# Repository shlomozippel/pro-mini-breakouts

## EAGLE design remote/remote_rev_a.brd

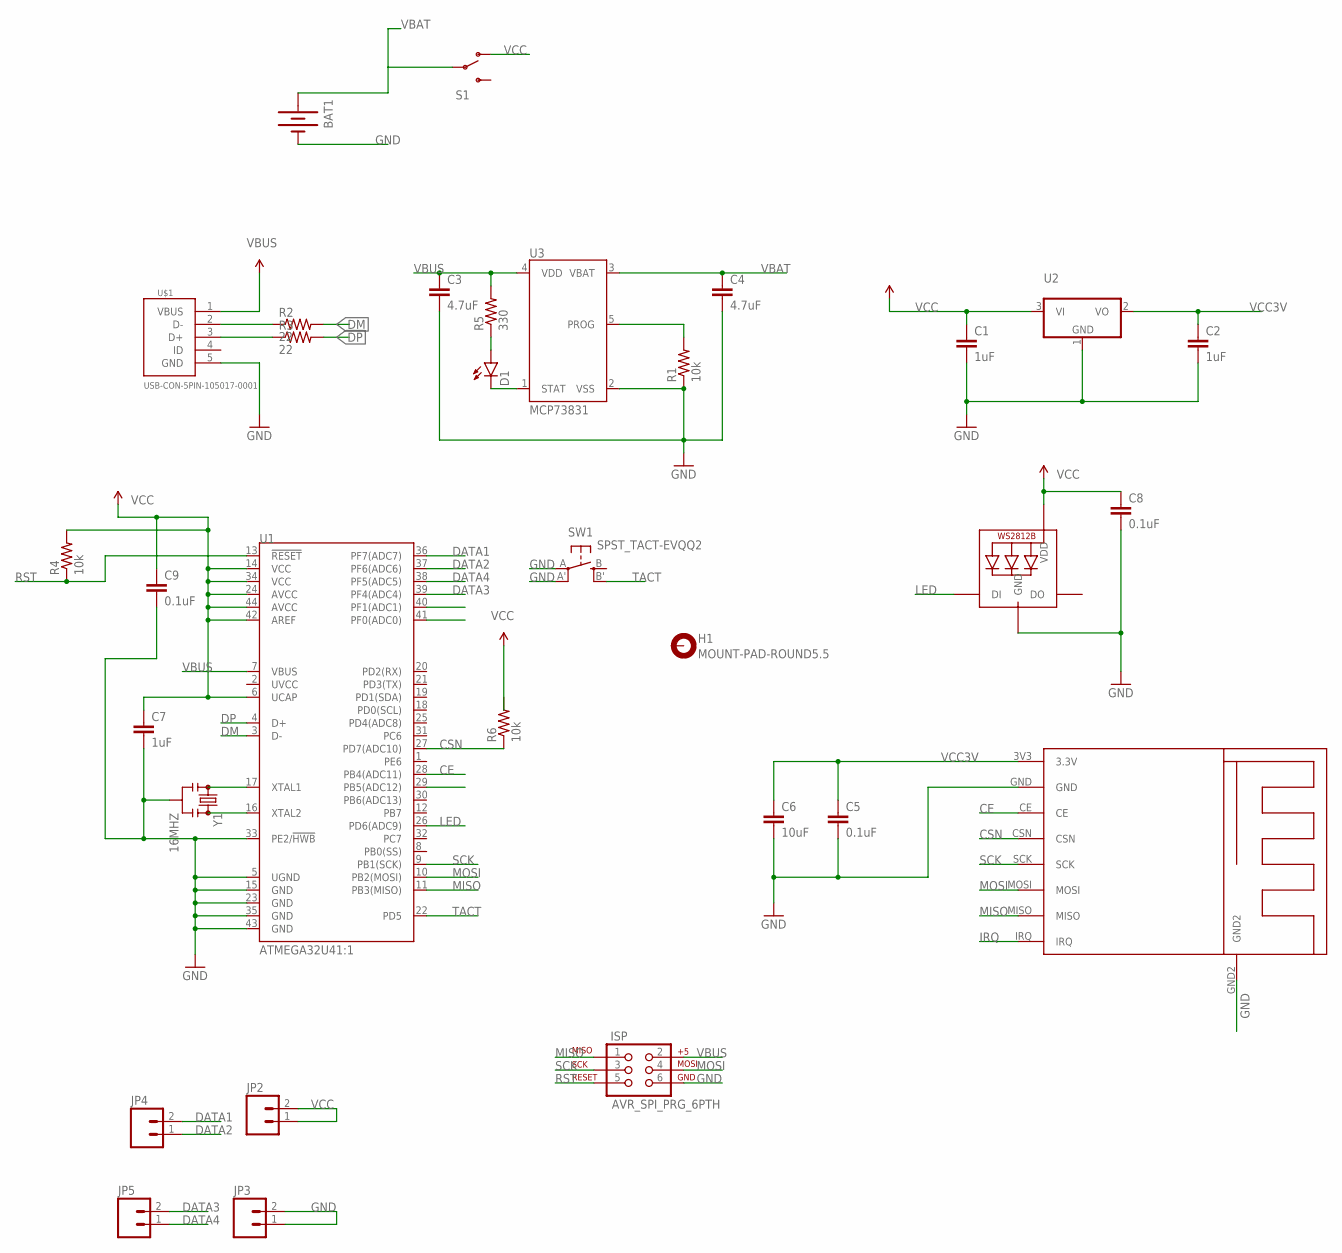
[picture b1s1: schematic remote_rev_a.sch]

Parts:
BAT1: BATTERY245PTH; BATTCON_245MM_PTH
C1, C2, C7: 1uF; 0603-CAP
C3, C4: 4.7uF; 0603-CAP
C5, C8, C9: 0.1uF; 0603-CAP
C6: 10uF; 0603-CAP
D1: LED0603; LED-0603
H1: MOUNT-PAD-ROUND5.5; 5,5-PAD
ISP: AVR_SPI_PRG_6PTH; 2X3
JP2, JP3, JP4, JP5: M02PTH; 1X02
LED1: WS2812B_5050N; WS2812B-NARROW
R1, R4, R6: 10k; 0603-RES
R2, R3: 22; 0603-RES
R5: 330; 0603-RES
S1: SWITCH-SPDTPTH; SWITCH-SPDT
SW1: SPST_TACT-EVQQ2; EVQ-Q2
U1: ATMEGA32U41:1; QFN-44-NOPAD_1:1
U2: AP2120N-3.0; SOT-23-3
U3: MCP73831; SOT23-5
U$1: USB-CON-5PIN-105017-0001; USB-MICRO-MOLEX-105017-0001
U$3: NRF24MINI
Y1: 16MHZ; RESONATOR-SMD

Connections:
CE: U1.28 (PB4(ADC11)), U$3.CE
CSN: R6.1, U1.27 (PD7(ADC10)), U$3.CSN
DATA1: JP4.2, U1.36 (PF7(ADC7))
DATA2: JP4.1, U1.37 (PF6(ADC6))
DATA3: JP5.2, U1.39 (PF4(ADC4))
DATA4: JP5.1, U1.38 (PF5(ADC5))
DM: R2.2, U1.3 (D-)
DP: R3.2, U1.4 (D+)
GND: BAT1.2 (-), C1.2, C2.2, C3.2, C4.2, C5.2, C6.2, C7.2, C8.2, C9.2, ISP.6, JP3.1, JP3.2, LED1.3-GND (GND), R1.1, SW1.A, SW1.A' (P1), U1.5 (UGND), U1.15 (GND), U1.23 (GND), U1.33 (PE2/!HWB), U1.35 (GND), U1.43 (GND), U2.1 (GND), U3.2 (VSS), U$1.5 (GND), U$3.GND, U$3.GND2, Y1.2
IRQ: U$3.IRQ
LED: LED1.4-DIN (DI), U1.26 (PD6(ADC9))
MISO: ISP.1, U1.11 (PB3(MISO)), U$3.MISO
MOSI: ISP.4, U1.10 (PB2(MOSI)), U$3.MOSI
unnamed: R1.2, U3.5 (PROG)
unnamed: R2.1, U$1.2 (D-)
unnamed: R3.1, U$1.3 (D+)
unnamed: U1.17 (XTAL1), Y1.1
unnamed: U1.16 (XTAL2), Y1.3
unnamed: D1.A, R5.1
unnamed: D1.C, U3.1 (STAT)
RST: ISP.5, R4.1, U1.13 (!RESET)
SCK: ISP.3, U1.9 (PB1(SCK)), U$3.SCK
TACT: SW1.B' (S1), U1.22 (PD5)
VBAT: BAT1.1 (+), BAT1.3 (+), C4.1, S1.2, U3.3 (VBAT)
VBUS: C3.1, ISP.2, R5.2, U1.7 (VBUS), U3.4 (VDD), U$1.1 (VBUS)
VCC: C1.1, C7.1, C8.1, C9.1, JP2.1, JP2.2, LED1.1-VDD (VDD), R4.2, S1.1 (O), U1.6 (UCAP), U1.14 (VCC), U1.24 (AVCC), U1.34 (VCC), U1.42 (AREF), U1.44 (AVCC), U2.3 (VI)
VCC3V: C2.1, C5.1, C6.1, U2.2 (VO), U$3.3V3 (3.3V)

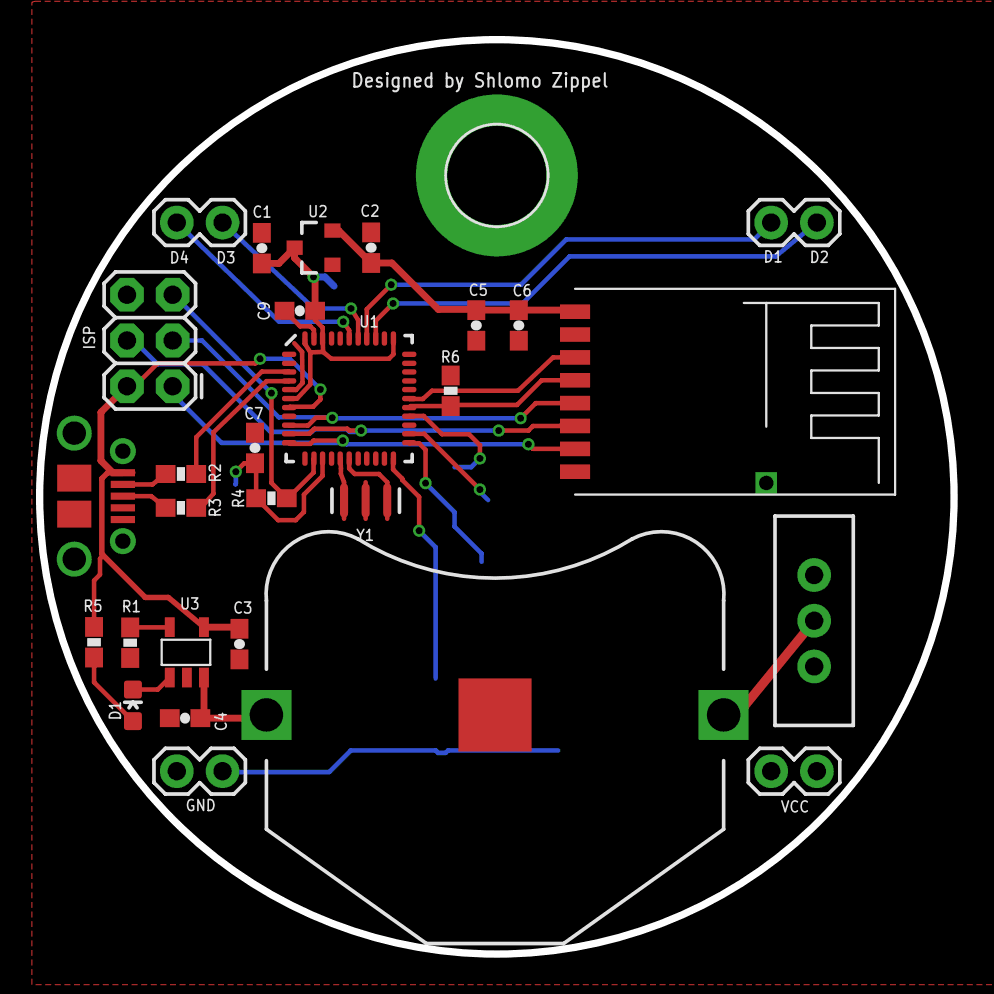
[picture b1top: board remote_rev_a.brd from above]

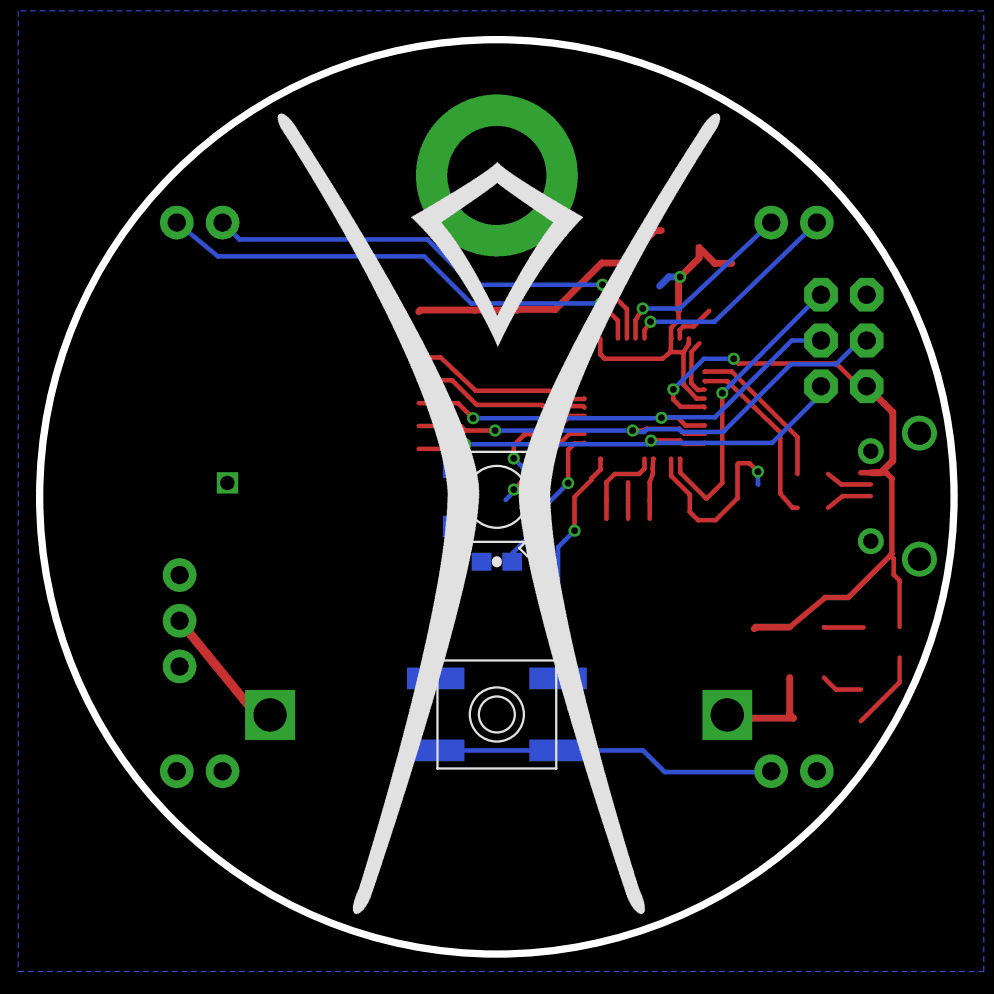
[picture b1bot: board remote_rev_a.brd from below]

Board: 2 copper layers, 50.8 x 50.8 mm, 32 parts (3 on the bottom side), 26 nets.

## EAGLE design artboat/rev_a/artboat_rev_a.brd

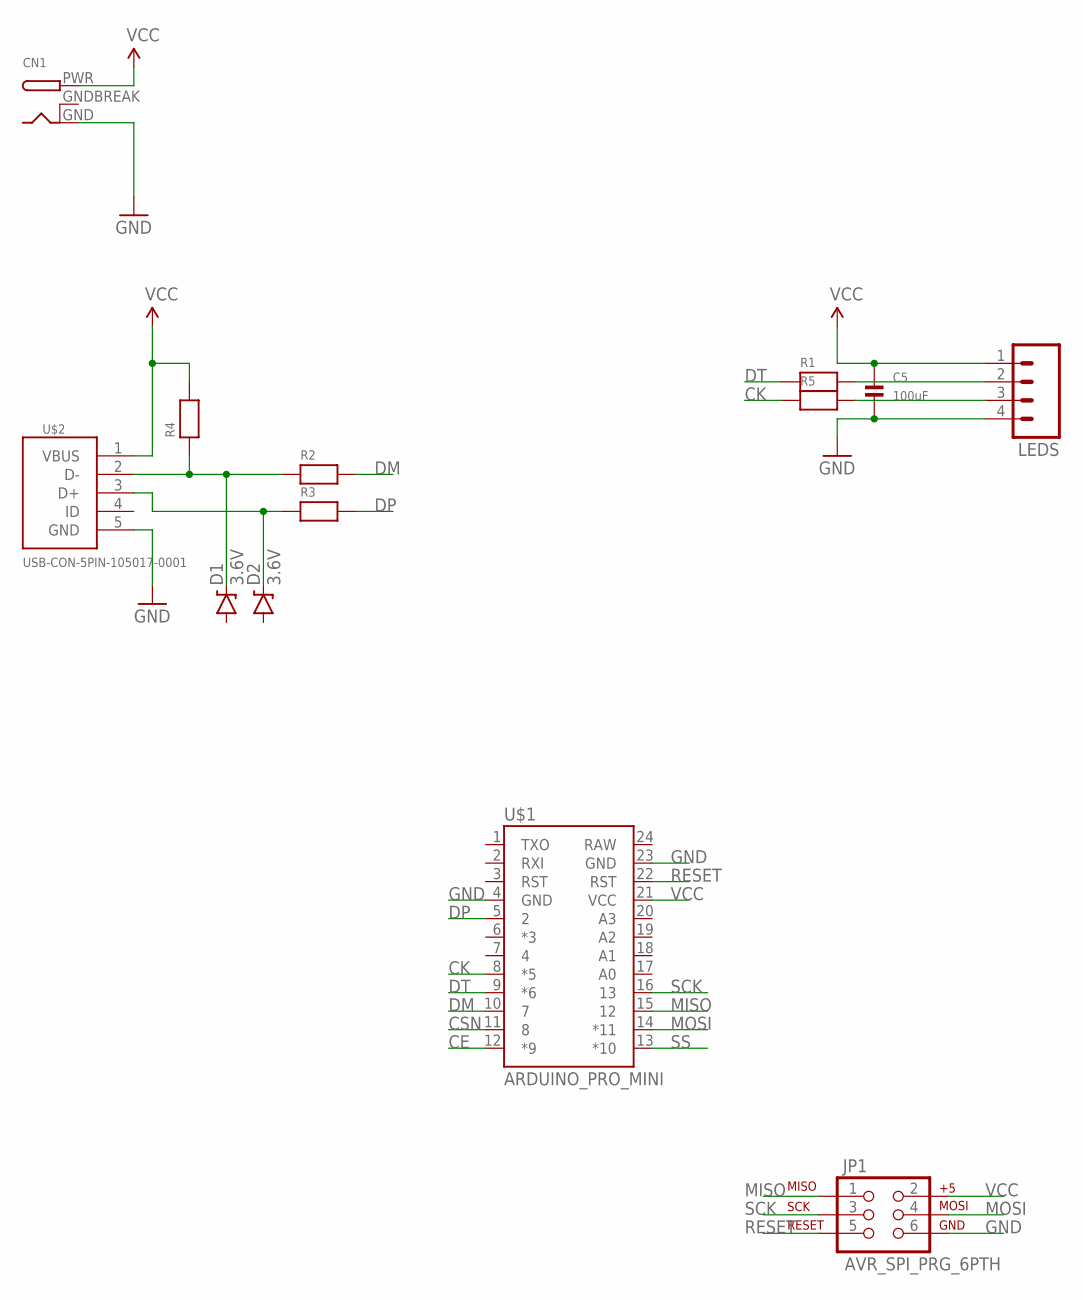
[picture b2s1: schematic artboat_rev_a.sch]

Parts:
C5: 100uF; 1206
CN1: DCBARRELPTH; DCJACK_2MM_PTH
D1, D2: 3.6V; SOD-323
JP1: AVR_SPI_PRG_6PTH; 2X3
LEDS: M04PTH; 1X04
R1, R2, R3, R4, R5: RESISTOR_0603; _0603
U$1: ARDUINO_PRO_MINI
U$2: USB-CON-5PIN-105017-0001; USB-MICRO-MOLEX-105017-0001

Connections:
CE: U$1.12 (*9)
CK: R5.1, U$1.8 (*5)
CSN: U$1.11 (8)
DM: R2.2, U$1.10 (7)
DP: R3.2, U$1.5 (2)
DT: R1.1, U$1.9 (*6)
GND: C5.2, CN1.GND, JP1.6, LEDS.4, U$1.4 (GND), U$1.23 (GND), U$2.5 (GND)
GNDBREAK: CN1.GNDBREAK
MISO: JP1.1, U$1.15 (12)
MOSI: JP1.4, U$1.14 (*11)
unnamed: LEDS.2, LEDS.3, R1.2, R5.2
unnamed: D1.C, R2.1, R4.1, U$2.2 (D-)
unnamed: D2.C, R3.1, U$2.3 (D+)
RESET: JP1.5, U$1.22 (RST)
SCK: JP1.3, U$1.16 (13)
SS: U$1.13 (*10)
VCC: C5.1, CN1.PWR, JP1.2, LEDS.1, R4.2, U$1.21 (VCC), U$2.1 (VBUS)

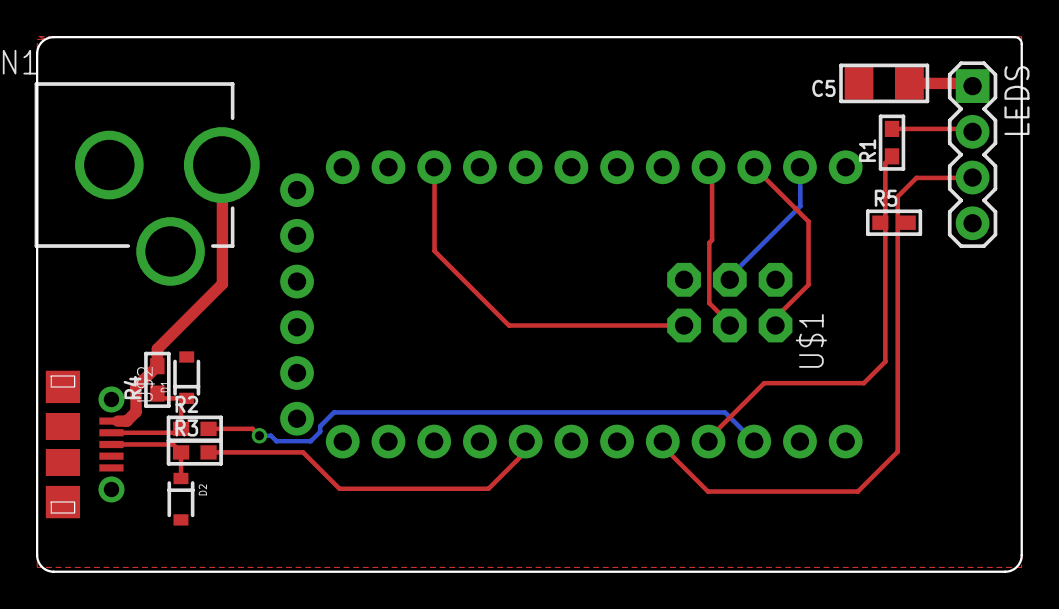
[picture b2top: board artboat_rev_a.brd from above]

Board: 2 copper layers, 54.7 x 29.7 mm, 14 parts (1 on the bottom side), 13 nets.

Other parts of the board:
U$5: 61*36-2

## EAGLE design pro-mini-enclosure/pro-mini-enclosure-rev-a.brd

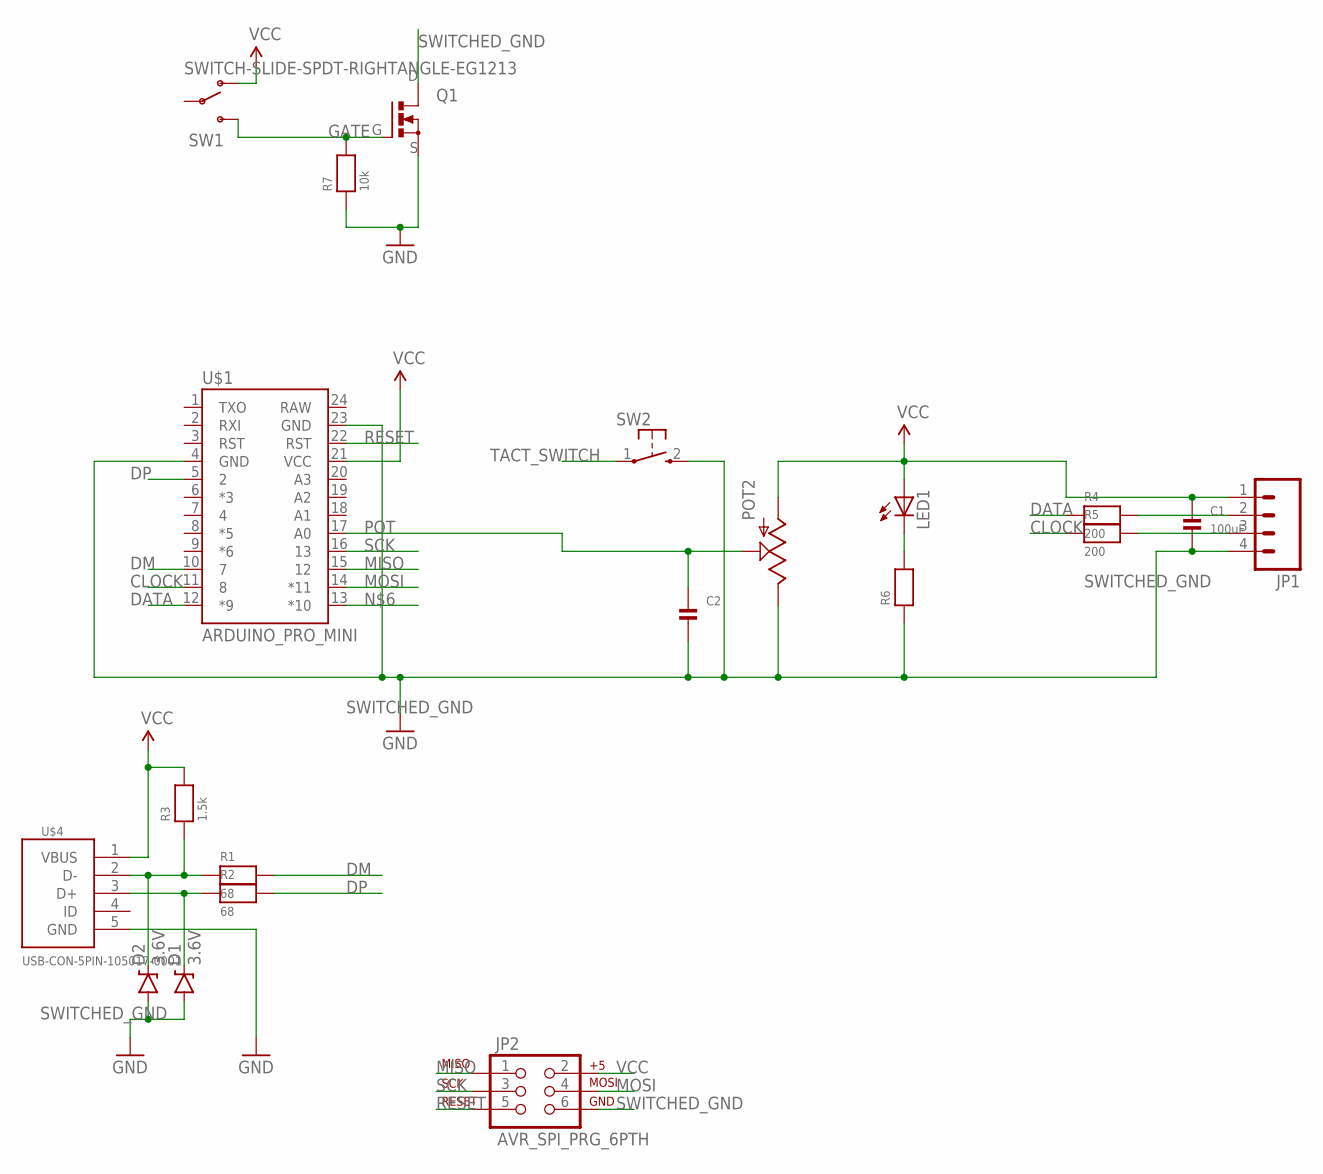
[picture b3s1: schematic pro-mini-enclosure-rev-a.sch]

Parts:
C1: 100uF; 1206
C2: CAP_CERAMIC0603MINI; 0603-MINI
D1, D2: 3.6V; SOD-323
JP1: M04PTH; 1X04
JP2: AVR_SPI_PRG_6PTH; 2X3
LED1: LEDCHIPLED_0603; CHIPLED_0603
POT2: THUMBWHEEL-POTENTIOMETER; 3352T
Q1: DMN1019USN; SC59
R1, R2: 68; 0603-MINI
R3: 1.5k; 0603-MINI
R4, R5: 200; 0603-MINI
R6: RESISTOR0603MINI; 0603-MINI
R7: 10k; 0603-MINI
SW1: SWITCH-SLIDE-SPDT-RIGHTANGLE-EG1213; SWITCH-SPDT-RIGHTANGLE-EG1213
SW2: TACTILE-SWITCH-1825027; 1825027
U$1: ARDUINO_PRO_MINI
U$4: USB-CON-5PIN-105017-0001; USB-MICRO-MOLEX-105017-0001

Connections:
CLOCK: R5.1, U$1.11 (8)
DATA: R4.1, U$1.12 (*9)
DM: R1.2, U$1.10 (7)
DP: R2.2, U$1.5 (2)
GATE: Q1.G, R7.2, SW1.3 (2)
GND: Q1.S, R7.1, U$4.5 (GND)
MISO: JP2.1, U$1.15 (12)
MOSI: JP2.4, U$1.14 (*11)
unnamed: D2.C, R1.1, R3.1, U$4.2 (D-)
unnamed: D1.C, R2.1, U$4.3 (D+)
unnamed: LED1.C, R6.2
unnamed: JP1.2, R4.2
unnamed: JP1.3, R5.2
POT: C2.1, POT2.2, U$1.17 (A0)
RESET: JP2.5, U$1.22 (RST)
SCK: JP2.3, U$1.16 (13)
SWITCHED_GND: C1.2, C2.2, D1.A, D2.A, JP1.4, JP2.6, POT2.3, Q1.D, R6.1, SW2.2 (3), U$1.4 (GND), U$1.23 (GND)
TACT_SWITCH: SW2.1
VCC: C1.1, JP1.1, JP2.2, LED1.A, POT2.1, R3.2, SW1.1, U$1.21 (VCC), U$4.1 (VBUS)

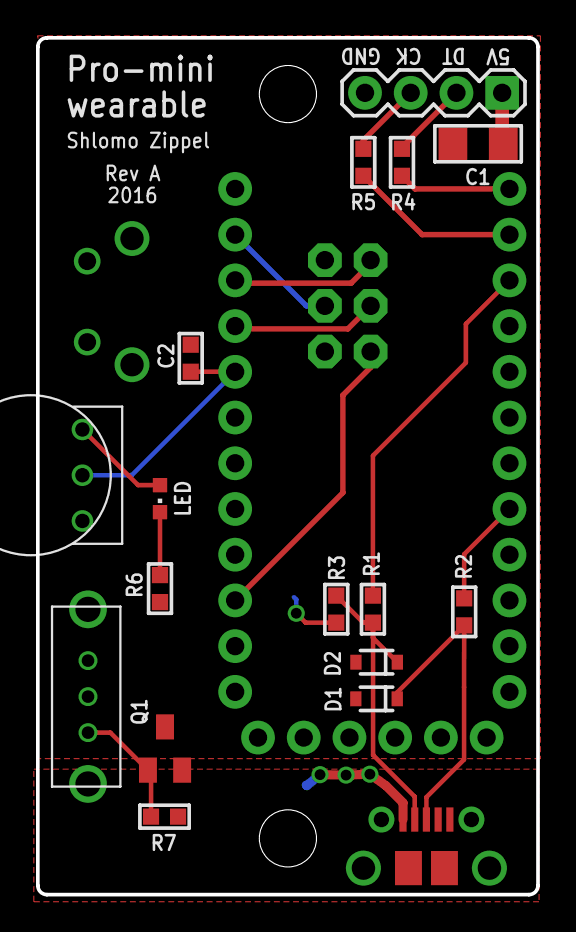
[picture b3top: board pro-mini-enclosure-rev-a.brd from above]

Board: 2 copper layers, 27.8 x 47.6 mm, 21 parts (1 on the bottom side), 18 nets.

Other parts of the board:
U$6: FB-30

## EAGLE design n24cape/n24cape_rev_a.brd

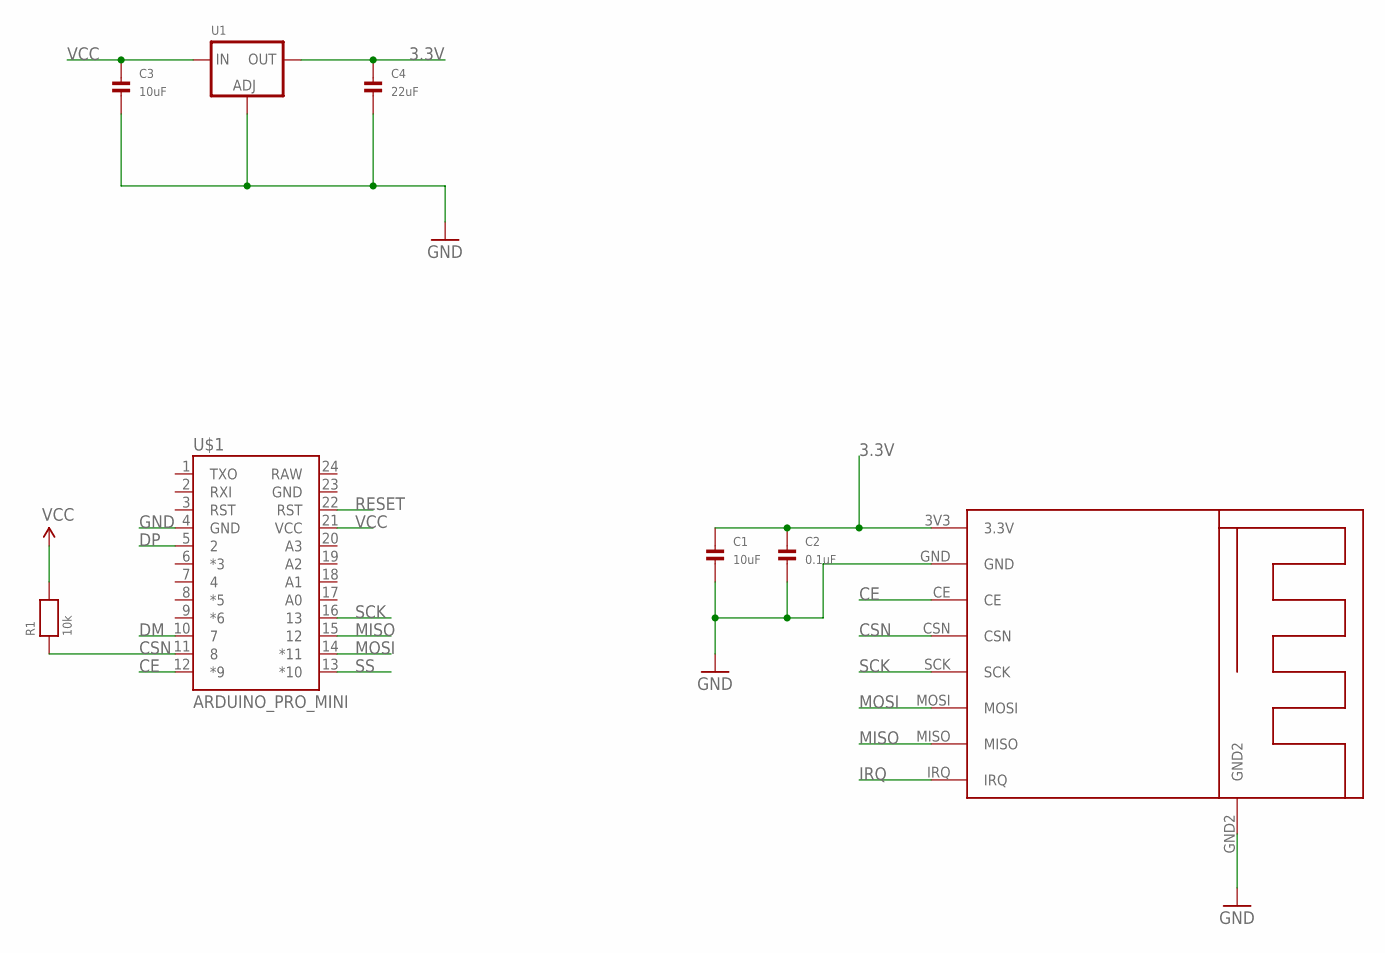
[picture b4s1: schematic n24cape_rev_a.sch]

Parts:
C1, C3: 10uF; 0603-MINI
C2: 0.1uF; 0603-MINI
C4: 22uF; 0603-MINI
R1: 10k; _0603
U1: LM1117SOT223-REFLOW; SOT223-R
U$1: ARDUINO_PRO_MINI
U$3: NRF24MINI

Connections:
3.3V: C1.1, C2.1, C4.1, U1.2 (OUT), U1.4 (OUT), U$3.3V3 (3.3V)
CE: U$1.12 (*9), U$3.CE
CSN: R1.1, U$1.11 (8), U$3.CSN
DM: U$1.10 (7)
DP: U$1.5 (2)
GND: C1.2, C2.2, C3.2, C4.2, U1.1 (ADJ), U$1.4 (GND), U$3.GND, U$3.GND2
IRQ: U$3.IRQ
MISO: U$1.15 (12), U$3.MISO
MOSI: U$1.14 (*11), U$3.MOSI
RESET: U$1.22 (RST)
SCK: U$1.16 (13), U$3.SCK
SS: U$1.13 (*10)
VCC: C3.1, R1.2, U1.3 (IN), U$1.21 (VCC)

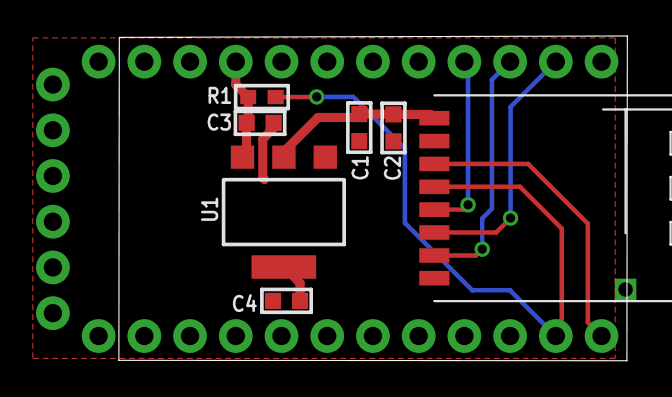
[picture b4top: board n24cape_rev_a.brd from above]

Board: 2 copper layers, 28.2 x 18.0 mm, 8 parts (0 on the bottom side), 8 nets.

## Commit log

2016-08-04 Added files to nrf24 remote

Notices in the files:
parts and their libraries:
SparkFun-Connectors: Licensing: Creative Commons ShareAlike 4.0 International - https://creativecommons.org/licenses/by-sa/4.0
microbuilder: This work is placed in the public domain, and may be freely used for commercial and non-commercial work with the following conditions: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
